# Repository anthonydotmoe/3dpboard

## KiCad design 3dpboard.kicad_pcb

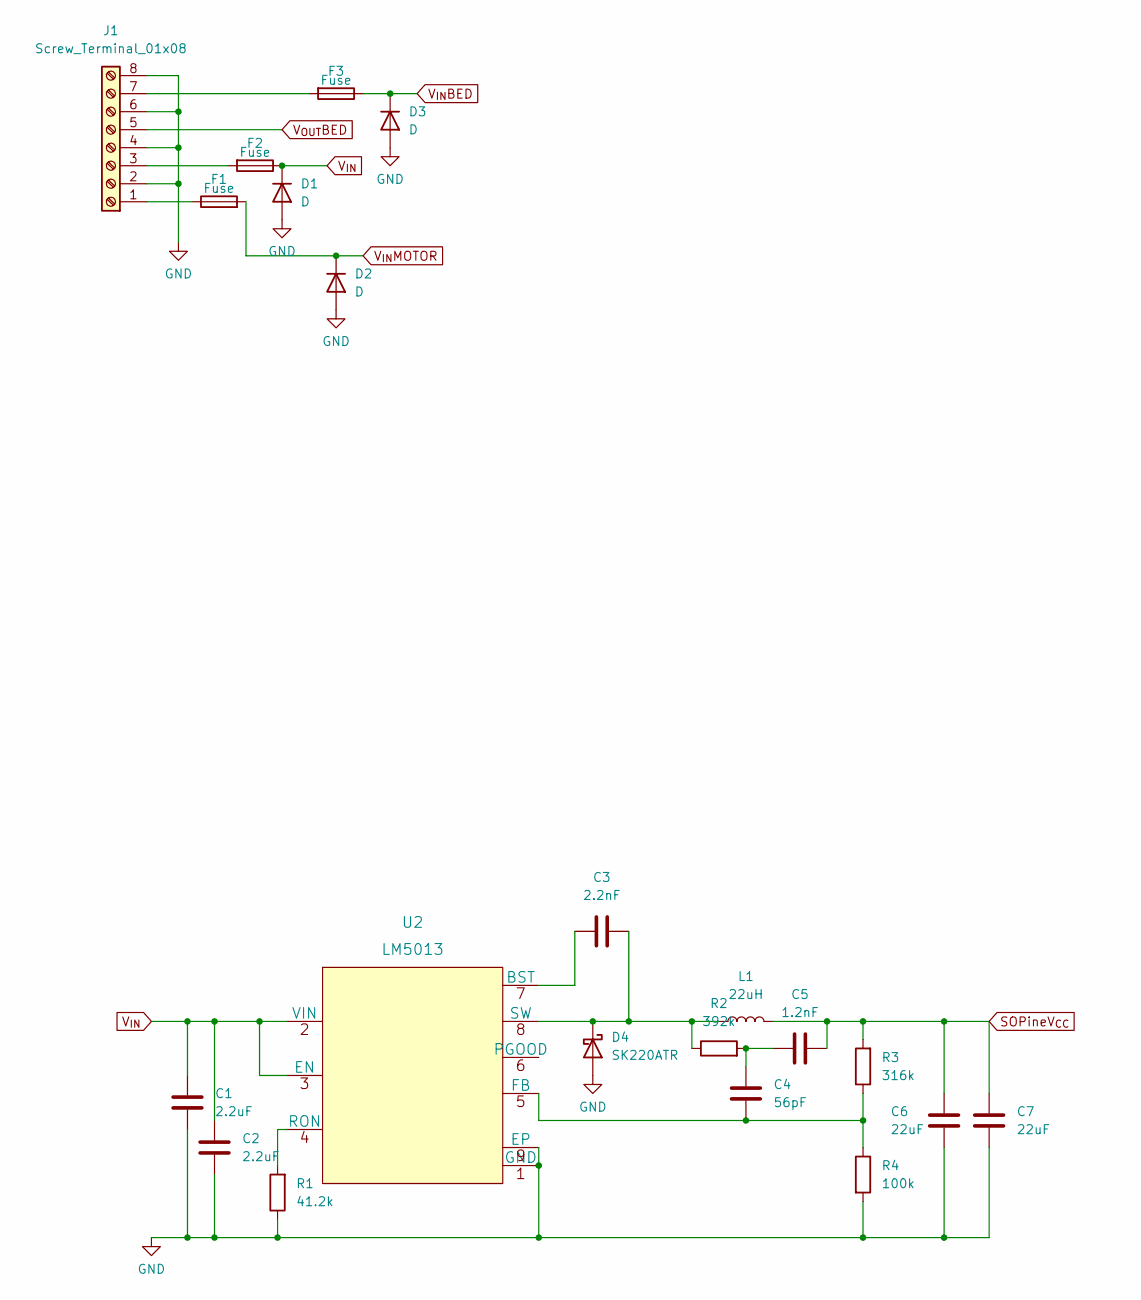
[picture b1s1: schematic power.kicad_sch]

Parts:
C1, C2: 2.2uF; C_1210_3225Metric; Part C3225X7R2A225K230AB
C3: 2.2nF; C_0402_1005Metric; Part CGA2B2X7R1H222K050BA
C4: 56pF; C_0805_2012Metric; Part CC0805JRNPO9BN560
C5: 1.2nF; C_0402_1005Metric; Part GRM155R71H122KA01D
C6, C7: 22uF; C_0603_1608Metric; Part C1608X5R1A226M080AC
D1, D2, D3: D; D_SMA
D4: SK220ATR; D_SMA
F1, F2, F3: Fuse; Fuseholder_Blade_Mini_Keystone_3568
J1: Screw_Terminal_01x08; OSTYK33108030; Part OSTYK33108030
L1: 22uH; Part SER1390-223MLB
R1: 41.2k; R_0402_1005Metric; Part CRCW040241K2FKED
R2: 392k; R_0603_1608Metric; Part CRCW0603392KFKEA
R3: 316k; R_0603_1608Metric; Part RC0603FR-07316KL
R4: 100k; R_0603_1608Metric; Part RC0603FR-07100KL
U2: LM5013; DDA0008E_N

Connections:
GND: C1.2, C2.2, C6.2, C7.2, D1.2 (A), D2.2 (A), D3.2 (A), D4.2 (A), J1.2, J1.4, J1.6, J1.8, R1.1, R4.2, U2.1 (GND), U2.9 (EP)
unnamed: C3.1, U2.7 (BST)
unnamed: C3.2, D4.1 (K), L1.1, R2.1, U2.8 (SW)
unnamed: C4.1, C5.1, R2.2
unnamed: C4.2, R3.1, R4.1, U2.5 (FB)
unnamed: F1.1, J1.1
unnamed: F2.2, J1.3
unnamed: F3.2, J1.7
unnamed: R1.2, U2.4 (RON)
SOPineV_{CC}: C5.2, C6.1, C7.1, L1.2, R3.2
V_{IN}: C1.1, C2.1, D1.1 (K), F2.1, U2.2 (VIN), U2.3 (EN)
V_{IN}BED: D3.1 (K), F3.1
V_{IN}MOTOR: D2.1 (K), F1.2
V_{OUT}BED: J1.5

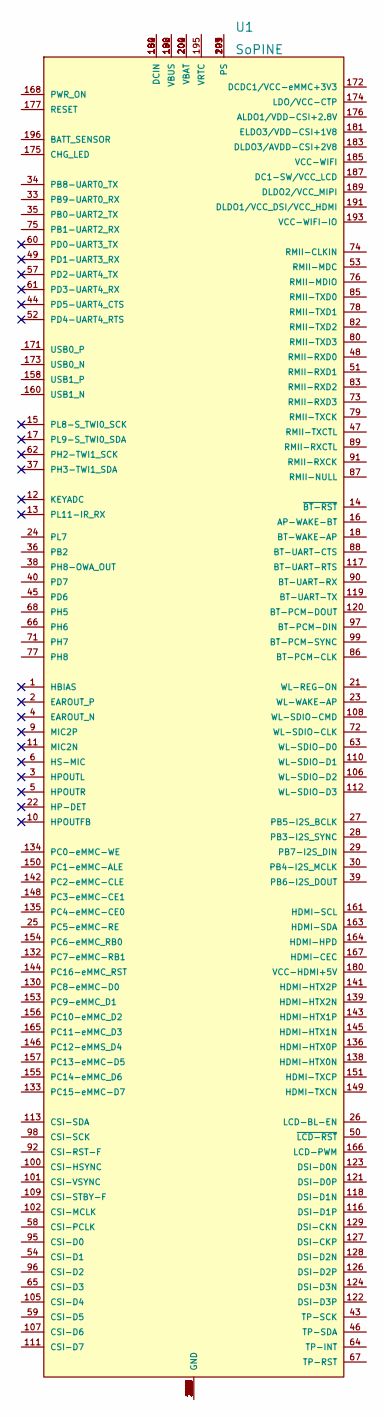
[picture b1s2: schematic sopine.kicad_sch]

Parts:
U1: SoPINE; 2-2013022-1

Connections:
unnamed: U1.7 (GND), U1.8 (GND), U1.19 (GND), U1.20 (GND), U1.31 (GND), U1.32 (GND), U1.41 (GND), U1.42 (GND), U1.55 (GND), U1.56 (GND), U1.69 (GND), U1.70 (GND), U1.81 (GND), U1.84 (GND), U1.93 (GND), U1.94 (GND), U1.103 (GND), U1.104 (GND), U1.114 (GND), U1.115 (GND), U1.125 (GND), U1.131 (GND), U1.137 (GND), U1.140 (GND), U1.147 (GND), U1.152 (GND), U1.159 (GND), U1.162 (GND), U1.169 (GND), U1.205 (GND), U1.206 (GND)
unnamed: U1.180 (DCIN), U1.182 (DCIN), U1.184 (DCIN)
unnamed: U1.188 (VBUS), U1.190 (VBUS), U1.192 (VBUS)
unnamed: U1.199 (PS), U1.201 (PS), U1.203 (PS)
unnamed: U1.200 (VBAT), U1.202 (VBAT), U1.204 (VBAT)

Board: 2 copper layers, 21 parts (0 on the bottom side), 18 nets, no tracks yet.

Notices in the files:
parts and their libraries:
Copyright 2021 Accelerated Designs. All rights reserved.
